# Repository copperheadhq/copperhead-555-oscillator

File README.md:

# 5 V Variable-Frequency 555 Oscillator, rev A

A compact bench oscillator. It gives an adjustable square wave from about 10 kHz to 1 MHz, for
an oscilloscope or a 5 V logic input. It is built around the TI TLC555 CMOS timer in astable
mode, followed by an SN74LVC1G17 Schmitt-trigger buffer. It runs from 5 V over USB-C. A
25-turn trimmer sets the frequency, and a slide switch picks one of two overlapping ranges.
The output is on a BNC and a 2-pin header. 60 × 35 mm, two layers, every part on the top.
For high-impedance loads only: no 50 Ω drive is claimed.

> ## ⚠ This board has never been built
>
> - **Never fabricated, never powered.** Nothing here has been tested on real hardware. Until
>   bring-up passes, every number below is a design value, not a measurement.
> - **Bare-PCB release.** Every part in [`docs/BOM.md`](docs/BOM.md) is still marked
>   UNVERIFIED, so rev A has no fab BOM. Assemble it by hand.
> - **The top of the range is at risk.** An ngspice study with TI's TLC555 model puts the
>   worst-case top of the HI range at about 744 kHz with the fitted C4 = 3.3 nF and
>   C6 = 330 pF. C4 = 2.2 nF and C6 = 150 pF reached 1.19 MHz at every corner. Both are 0603
>   C0G parts, so the choice can be made at assembly (see [`fab/rev-a/README.md`](fab/rev-a/README.md)).
> - **Not checked:** parts against datasheets and stock, the gerbers in a viewer, the fab's DFM
>   report, EMC and temperature behaviour.
>
> Passing ERC and DRC means the copper matches the schematic and a rule set. It is not evidence
> that the circuit works.

*Renders, not photographs, with every footprint populated.*

## The circuit

- **Power entry:** a GCT USB4105 USB-C receptacle, used for 5 V only. CC1 and CC2 each have
  their own 5.1 kΩ pull-down. A TPD1E10B06 ESD diode and a 10 µF capacitor sit on VBUS. There
  is no regulator and no battery. The budget is below 30 mA.
- **Timer core:** a TLC555 astable with R_A = 1.00 kΩ and R_B = 120 Ω plus a Bourns 3296W
  100 kΩ 25-turn trimmer (RV1), wired as a rheostat.
  - A C&K JS102011SCQN top-slide switch (SW1) picks the timing capacitor: C4 for LO or C6 for
    HI, both C0G.
  - SW1 sits in the capacitors' ground return, so no switch contact touches the timing node.
  - 1 % resistors; 100 nF decoupling at the timer and 10 nF on CONT.
- **Output buffer:** an SN74LVC1G17 Schmitt buffer squares up the timer output, with a 33 Ω
  series resistor to the output. The 33 Ω damps cable ringing. It is not a 50 Ω match.
- **Output connectors:** an Amphenol RF B6252HB right-angle BNC at the right board edge, and a
  Samtec TSW 2-pin header (pin 1 OUT, pin 2 GND).
- **Indicators:** a green power LED, and a green activity LED driven from the buffer output,
  two stages away from the timing node.
- **Test points:** five bare pads, for 5V, GND, TIMING, RAW (timer output) and OUT. The
  silkscreen warns that a probe on TIMING shifts the frequency.

### Frequency ranges

| Range | Switch | Timing C | Worst case, hand calculation | Worst-case top, ngspice |
| --- | --- | --- | --- | --- |
| LO | `LO 10–100 kHz` | C4 3.3 nF | 2.54 kHz to 120.6 kHz | — |
| HI | `HI 100 kHz–1 MHz` | C6 330 pF | 25.4 kHz to 1.206 MHz | about 744 kHz |

The hand calculation is the ideal astable equation at worst-case tolerances (from
[`docs/SUBSYSTEMS.md`](docs/SUBSYSTEMS.md)). It leaves out the TLC555's internal delays, about
370 ns per cycle, which matter near 1 MHz. Within each range, most of the trimmer's travel
tunes the low end, because frequency goes as 1/R.

The design documents are in [`docs/`](docs/):

- [`BRIEF.md`](docs/BRIEF.md): what was asked for.
- [`SPEC.md`](docs/SPEC.md): the specification derived from the brief.
- [`SUBSYSTEMS.md`](docs/SUBSYSTEMS.md): the circuit, block by block, with the timing arithmetic.
- [`PINOUT.md`](docs/PINOUT.md): the connectors and test points.
- [`BOM.md`](docs/BOM.md): every part and its reason. Every MPN is unverified.
- [`DECISIONS.md`](docs/DECISIONS.md): the design's decisions.

### The board

From [`docs/BOARD-STATS.md`](docs/BOARD-STATS.md):

- **Size:** 60 x 35 mm, 1.6 mm thick, two M3 mounting holes.
- **Stackup:** two copper layers. GND pours on both, and the back is an unbroken ground plane
  under the oscillator and output path.
- **Parts:** 30 footprints, all on the top: 20 SMD, 3 through-hole (J2, J3, RV1), and the test
  pads and mounting holes. 23 are parts to fit.
- **Routing:** 18 vias (0.3 mm drill), 15 nets, 68 track segments, all on the top layer,
  0.2 to 0.4 mm wide.

## Layout of this repository

```text
hardware/   KiCad project: schematic, board, design rules, vendored symbols, the SW1 footprint and model
docs/       brief, design documents, board statistics, schematic as PDF and SVG
fab/        gerbers, drill and placement file for rev A (read the README in the folder)
images/     renders of the board, not photographs
3d/         STEP, GLB and STL models
LICENSES/   full text of the licences below
```

## Building it

1. **Open:** use KiCad 10.0.6 or later on
   `hardware/5-v-variable-frequency-555-oscillator.kicad_pro`. The symbols are vendored in
   `hardware/sym-lib-cache/` (through `sym-lib-table`). The SW1 footprint and 3D model are in
   `hardware/lib/` (through `fp-lib-table`). It opens without extra libraries.
2. **Fab files:** read [`fab/rev-a/README.md`](fab/rev-a/README.md) first. The files are the
   rev A release unchanged, and the README lists what has not been checked.
3. **Order bare boards:** two layers, 1.6 mm. Nothing special on the order form.
4. **Parts:** buy them from [`docs/BOM.md`](docs/BOM.md). Check each against its datasheet
   first, because none has been checked yet. Fit the **B6252HB-NPP3G-50** BNC, which is the
   footprint on the board, not the 31-5536-RFX the brief names. Decide C4 and C6 (see above).
5. **Assemble by hand:** the placement file in `fab/rev-a/` gives every part's position and
   rotation. J2, J3 and RV1 are through-hole.

## Licence

| What | Licence |
|---|---|
| Hardware: everything under `hardware/`, `fab/` and `3d/` | **CERN-OHL-S-2.0** (strongly reciprocal) |
| Documentation and images: `docs/`, `images/`, `README.md` | **CC-BY-4.0** |

Full texts are in [`LICENSES/`](LICENSES/). See [`LICENSE`](LICENSE) for the per-directory
statement.

**No warranty.** CERN-OHL-S-2.0 sections 8 and 9 apply: no warranty, no liability.

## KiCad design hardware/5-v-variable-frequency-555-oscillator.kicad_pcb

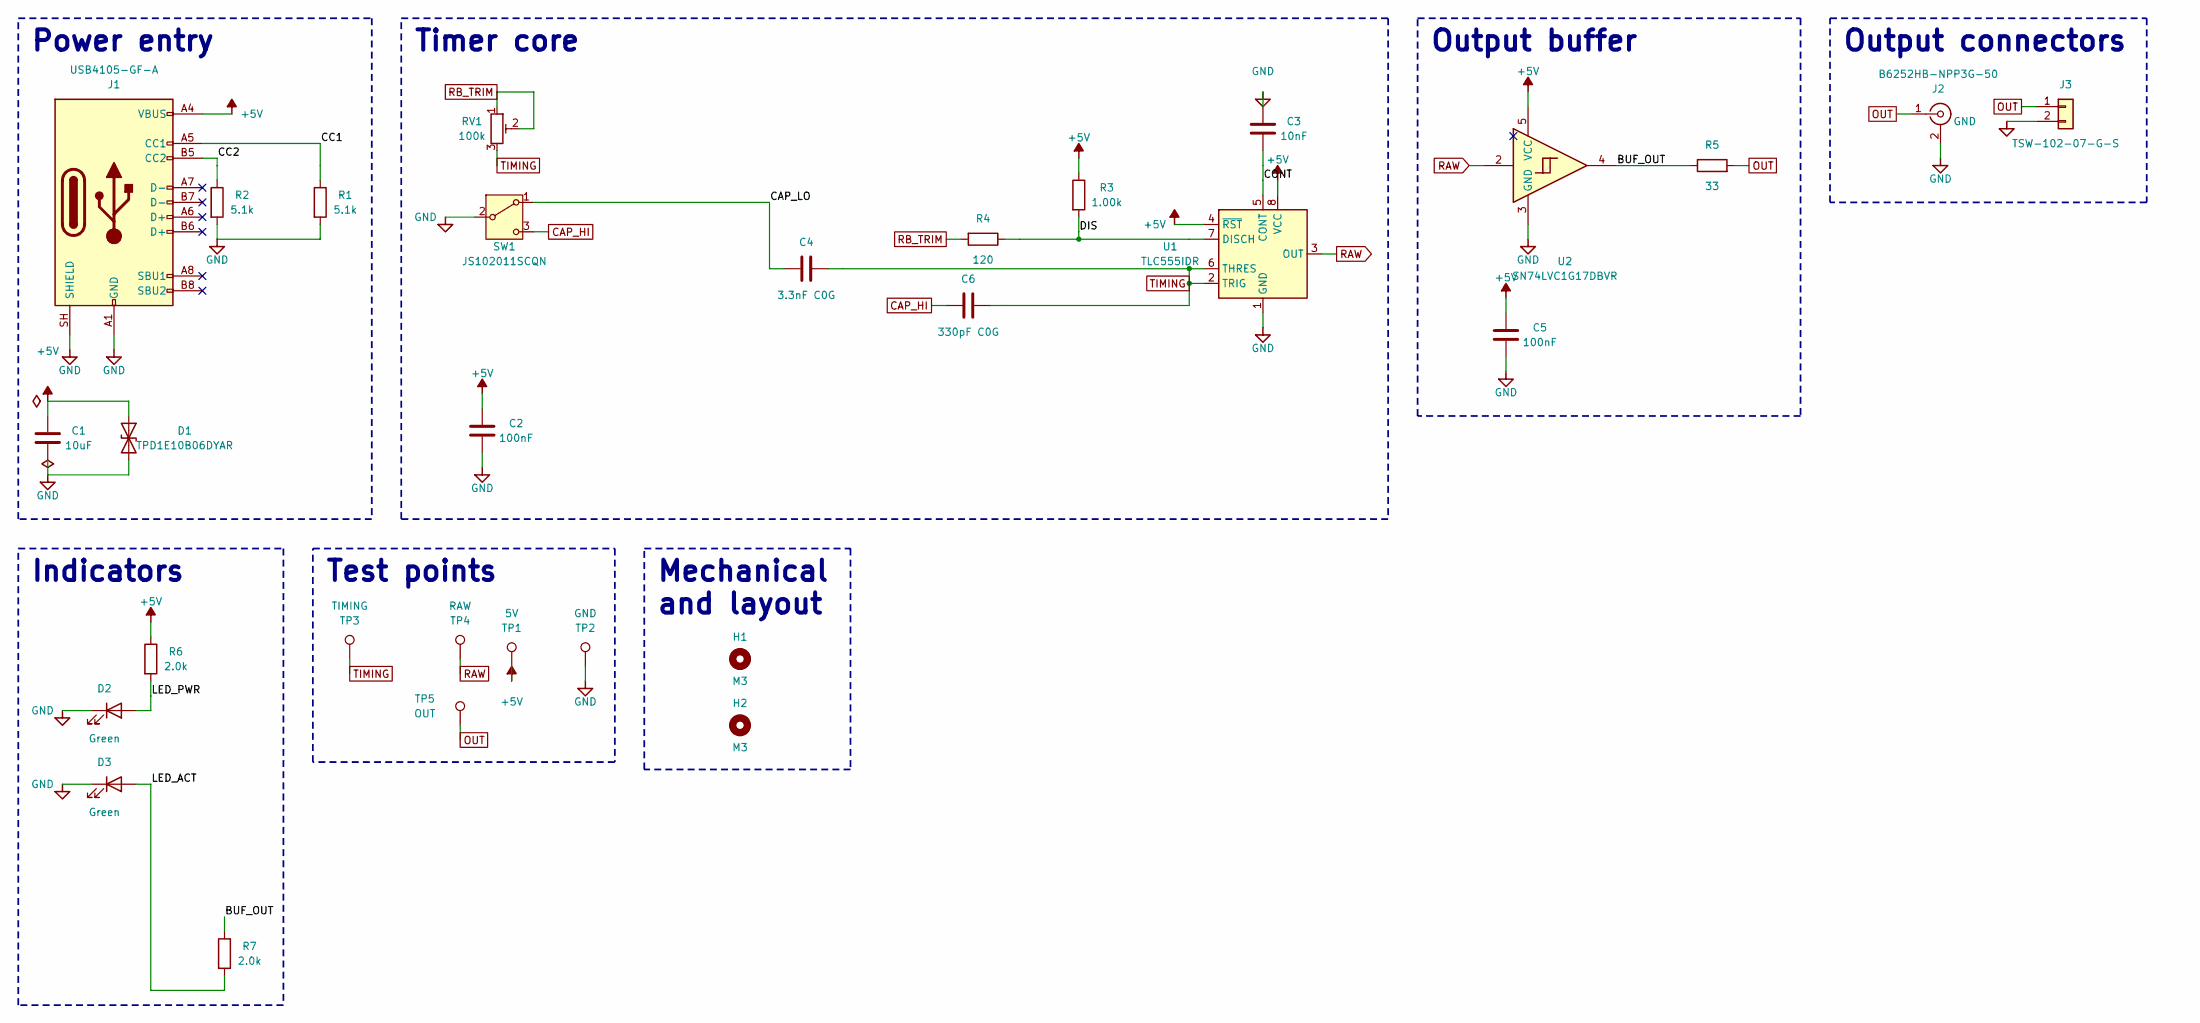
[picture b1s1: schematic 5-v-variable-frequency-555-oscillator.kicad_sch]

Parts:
C1: 10uF; C_0805_2012Metric
C2, C5: 100nF; C_0603_1608Metric
C3: 10nF; C_0603_1608Metric
C4: 3.3nF C0G; C_0603_1608Metric
C6: 330pF C0G; C_0603_1608Metric
D1: TPD1E10B06DYAR; D_SOD-523
D2, D3: Green; LED_0603_1608Metric
H1, H2: M3; MountingHole_3.2mm_M3
J1: USB4105-GF-A; USB_C_Receptacle_GCT_USB4105-xx-A_16P_TopMnt_Horizontal
J2: B6252HB-NPP3G-50; BNC_Amphenol_B6252HB-NPP3G-50_Horizontal
J3: TSW-102-07-G-S; PinHeader_1x02_P2.54mm_Vertical
R1, R2: 5.1k; R_0603_1608Metric
R3: 1.00k; R_0603_1608Metric
R4: 120; R_0603_1608Metric
R5: 33; R_0603_1608Metric
R6, R7: 2.0k; R_0603_1608Metric
RV1: 100k; Potentiometer_Bourns_3296W_Vertical
SW1: JS102011SCQN; SW_SPDT_CK_JS102011SCQN
TP1: 5V; TestPoint_Pad_D1.5mm
TP2: GND; TestPoint_Pad_D1.5mm
TP3: TIMING; TestPoint_Pad_D1.5mm
TP4: RAW; TestPoint_Pad_D1.5mm
TP5: OUT; TestPoint_Pad_D1.5mm
U1: TLC555IDR; SOIC-8_3.9x4.9mm_P1.27mm
U2: SN74LVC1G17DBVR; SOT-23-5

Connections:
+5V: C1.1, C2.1, C5.1, D1.1 (A1), J1.A4 (VBUS), J1.A9 (VBUS), J1.B4 (VBUS), J1.B9 (VBUS), R3.1, R6.1, TP1.1, U1.4 (~RST), U1.8 (VCC), U2.5 (VCC)
/BUF_OUT: R5.1, R7.1, U2.4
/CAP_LO: C4.2, SW1.1 (A)
/CC1: J1.A5 (CC1), R1.1
/CC2: J1.B5 (CC2), R2.1
/CONT: C3.1, U1.5 (CONT)
/DIS: R3.2, R4.1, U1.7 (DISCH)
/LED_ACT: D3.2 (A), R7.2
/LED_PWR: D2.2 (A), R6.2
CAP_HI: C6.2, SW1.3 (C)
GND: C1.2, C2.2, C3.2, C5.2, D1.2 (A2), D2.1 (K), D3.1 (K), J1.A1 (GND), J1.A12 (GND), J1.B1 (GND), J1.B12 (GND), J1.SH (SHIELD), J2.2 (Ext), J3.2, R1.2, R2.2, SW1.2 (B), TP2.1, U1.1 (GND), U2.3 (GND)
OUT: J2.1 (In), J3.1, R5.2, TP5.1
RAW: TP4.1, U1.3 (OUT), U2.2
RB_TRIM: R4.2, RV1.1, RV1.2
TIMING: C4.1, C6.1, RV1.3, TP3.1, U1.2 (TRIG), U1.6 (THRES)

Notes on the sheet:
Indicators
Mechanical and layout
Output buffer
Output connectors
Power entry
Test points
Timer core

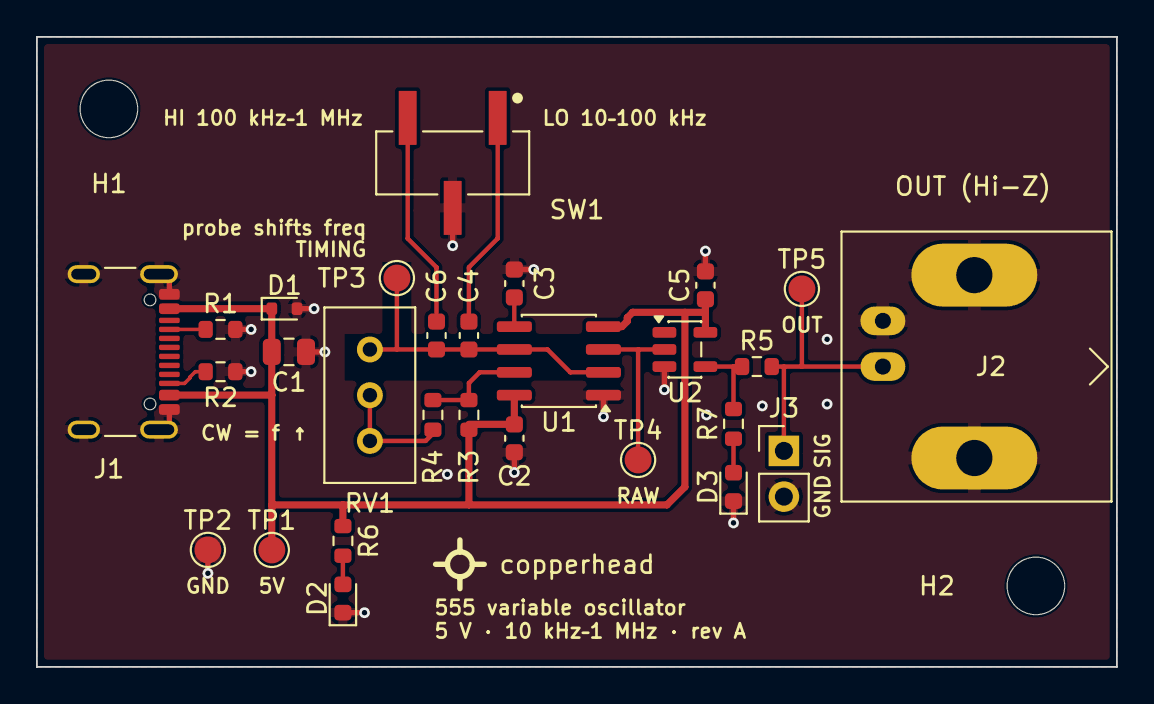
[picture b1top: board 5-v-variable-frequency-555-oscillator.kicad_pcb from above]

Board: 2 copper layers, 60.0 x 35.0 mm, 30 parts (0 on the bottom side), 15 nets.
